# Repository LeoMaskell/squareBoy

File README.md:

# macropad
a macropad! Yet to get the stuff from hackclub as the form is down.

## shell:
- made of abs plastic, constructed with 2 parts, the base and the lid and 4x m3 screws
- onshape document: https://cad.onshape.com/documents/8ea4270e3df64d720bc8c49e/w/e0b07a3a483165cebf54e193/e/cd51b0c8f39a18b2551e130c

## PCB:
- designed in kicad
- 2 layer pcb

## parts list:
- 1x Seeed XIAO RP2040
- 9x through-hole 1N4148 Diodes
- 9x MX-Style switches
- 1x EC11 Rotary encoders
- 1x 0.91 inch OLED display (the pin order is GND-VCC-SCL-SDA, MAKE SURE YOUR PCB MATCHES)
- 9x white blank DSA keycaps
- 4x M3x16mm screws
- 1 PCB
- 2 3d printed parts for the case (dark blue ABS for base plate, light blue ABS for top of shell)

## credits:
- macropad from the website hackpad.hackclub.com -> alex ren, dari.zone
- kicad
- onshape

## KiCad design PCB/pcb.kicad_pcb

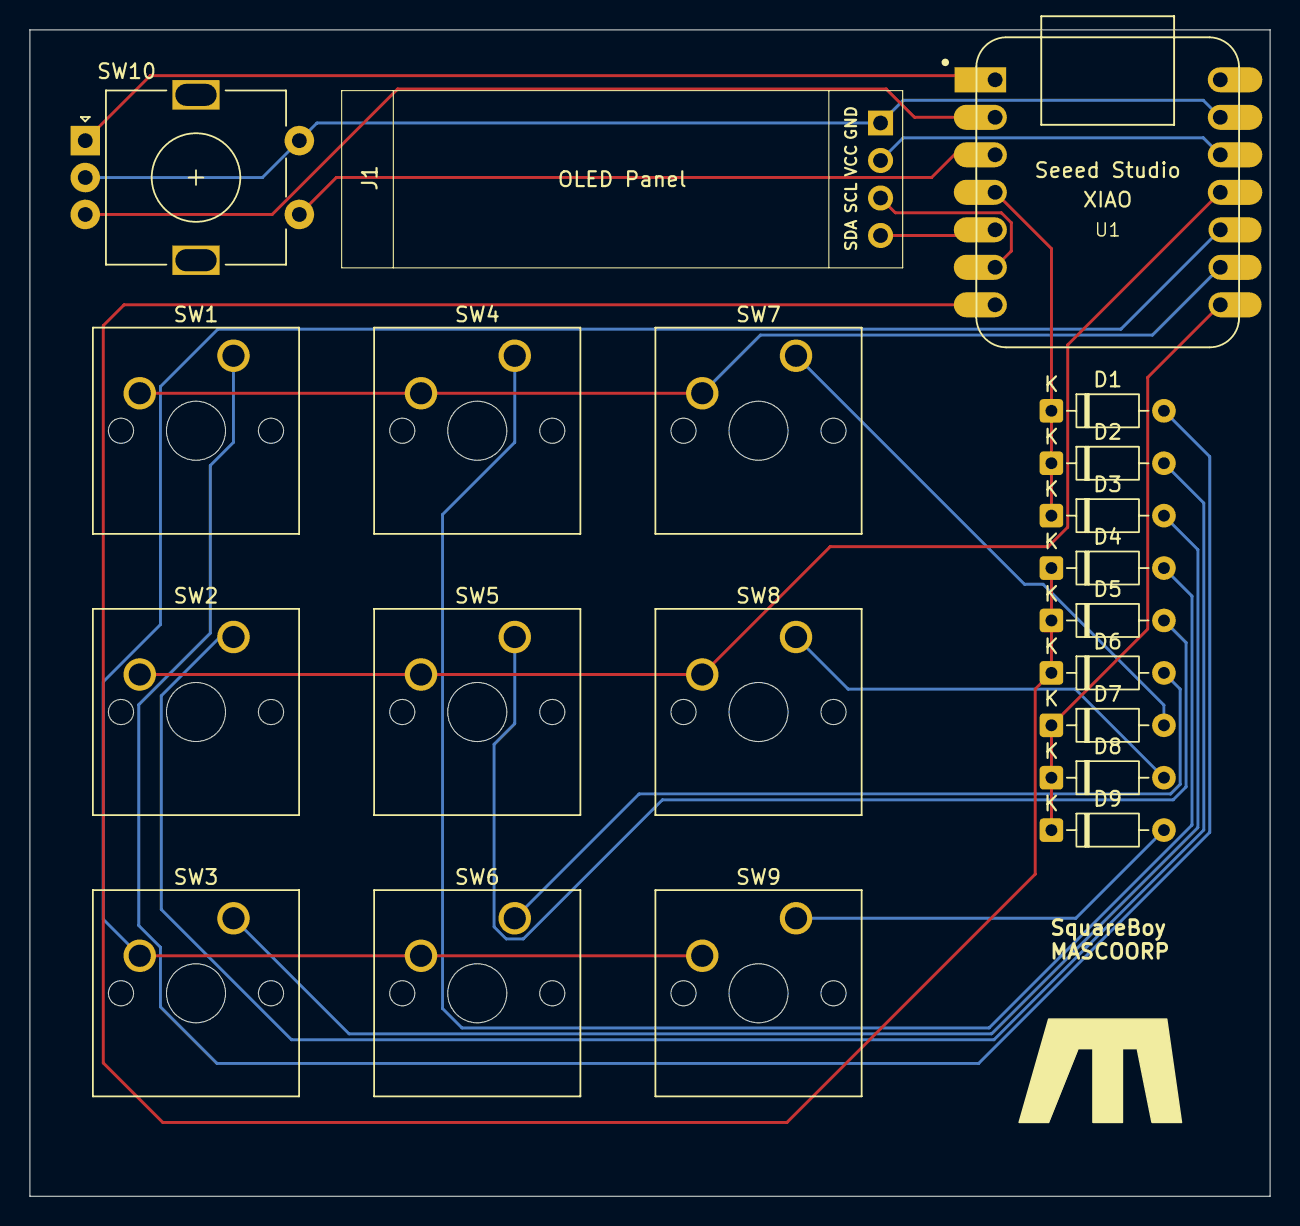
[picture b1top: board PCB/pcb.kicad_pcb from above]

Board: 2 copper layers, 84.0 x 79.0 mm, 21 parts (0 on the bottom side), 22 nets.

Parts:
D1, D2, D3, D4, D5, D6, D7, D8, D9: 1N4148; D_DO-35_SOD27_P7.62mm_Horizontal
J1: Conn_01x04_Pin; SSD1306-0.91-OLED-4pin-128x32(1)
SW1, SW2, SW3, SW4, SW5, SW6, SW7, SW8, SW9: SW_Push; SW_Cherry_MX_1.00u_PCB
SW10: RotaryEncoder_Switch; RotaryEncoder_Alps_EC11E-Switch_Vertical_H20mm
U1: MOUDLE-SEEEDUINO-XIAO; XIAO-Generic-Hybrid-14P-2.54-21X17.8MM

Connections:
unnamed: D1.2 (A), SW1.1
unnamed: D1.1 (K), D2.1 (K), D3.1 (K), U1.4 (PA11_A3_D3)
unnamed: D2.2 (A), SW2.1
unnamed: D3.2 (A), SW3.1
unnamed: D4.2 (A), SW4.1
unnamed: D4.1 (K), D5.1 (K), D6.1 (K), U1.7 (PB08_A6_D6_TX)
unnamed: D5.2 (A), SW5.1
unnamed: D6.2 (A), SW6.1
unnamed: D7.2 (A), SW7.1
unnamed: D7.1 (K), D8.1 (K), D9.1 (K), U1.8 (PB09_A7_D7_RX)
unnamed: D8.2 (A), SW8.1
unnamed: D9.2 (A), SW9.1
unnamed: J1.1, SW10.C, SW10.S2, U1.13 (GND)
unnamed: J1.2, U1.12 (3V3)
unnamed: J1.3, U1.6 (PA9_A5_D5_SCL)
unnamed: J1.4, U1.5 (PA8_A4_D4_SDA)
unnamed: SW10.A, U1.1 (PA02_A0_D0)
unnamed: SW10.B, U1.2 (PA4_A1_D1)
unnamed: SW3.2, SW6.2, SW9.2, U1.10 (PA5_A9_D9_MISO)
unnamed: SW2.2, SW5.2, SW8.2, U1.11 (PA6_A10_D10_MOSI)
unnamed: SW1.2, SW4.2, SW7.2, U1.9 (PA7_A8_D8_SCK)
unnamed: SW10.S1, U1.3 (PA10_A2_D2)

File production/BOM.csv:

"Id";"Designator";"Footprint";"Quantity";"Designation";"Supplier and ref";
1;"D1, D2, D3, D4, D5, D6, D7, D8, D9";"D_DO-35_SOD27_P7.62mm_Horizontal";9;"1N4148";;;
2;"J1";"SSD1306-0.91-OLED-4pin-128x32(1)";1;"Conn_01x04_Pin";;;
3;"SW1, SW2, SW3, SW4, SW5, SW6, SW7, SW8, SW9";"SW_Cherry_MX_1.00u_PCB";9;"SW_Push";;;
4;"SW10";"RotaryEncoder_Alps_EC11E-Switch_Vertical_H20mm";1;"RotaryEncoder_Switch";;;
5;"U1";"XIAO-Generic-Hybrid-14P-2.54-21X17.8MM";1;"MOUDLE-SEEEDUINO-XIAO";;;

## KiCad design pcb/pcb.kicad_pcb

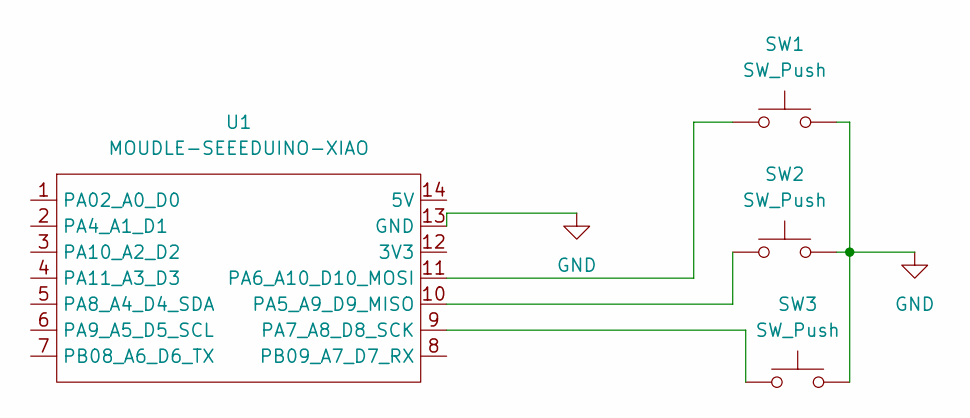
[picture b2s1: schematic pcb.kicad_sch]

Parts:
SW1, SW2, SW3: SW_Push; SW_Cherry_MX_1.00u_PCB
U1: MOUDLE-SEEEDUINO-XIAO; XIAO-Generic-Hybrid-14P-2.54-21X17.8MM

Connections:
GND: SW1.2, SW2.2, SW3.2, U1.13 (GND)
unnamed: SW2.1, U1.10 (PA5_A9_D9_MISO)
unnamed: SW1.1, U1.11 (PA6_A10_D10_MOSI)
unnamed: SW3.1, U1.9 (PA7_A8_D8_SCK)

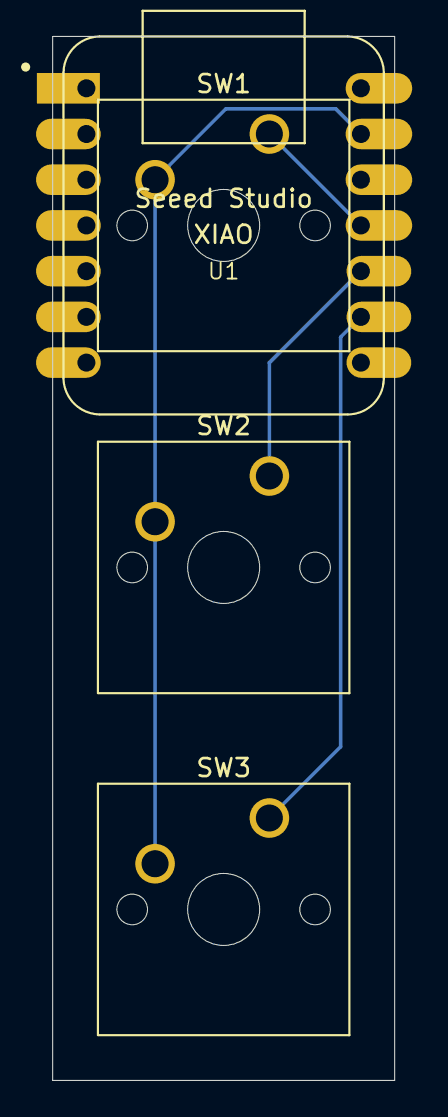
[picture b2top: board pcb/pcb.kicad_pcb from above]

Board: 2 copper layers, 19.0 x 58.0 mm, 4 parts (0 on the bottom side), 4 nets.

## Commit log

2026-06-05 added the pcb
    FIRST PCB!!!!
2026-06-05 finnished pcb, working on the case design for V1
2026-06-06 finnished the template
    TODOL: updae README
2026-06-07 finnished v2
    TODO: V3
    TODO: make pretty and export the onshape files
2026-06-08 Expand README with macropad details
    Added detailed information about the macropad including shell, PCB design, parts list, and credits.
2026-06-08 finnished 3d models etc
2026-06-08 added a release for the demo
2026-06-08 Update README with Onshape document link
    Added Onshape document link for shell design.
2026-06-14 editted PCB
    - added fillets
    - added a silkscreen
    - COMPANY NAME = MASCOORP
    - rewired
    - fixed switch spacing
2026-06-16 added some pcb stuff
    TODO: organise for the thing
2026-06-16 fixed CAD section of the files
2026-06-16 sorted out folders
2026-06-16 finished production except for firmware
2026-06-16 added a BOM for the readme
2026-06-16 Update kit components in README
    Added additional components and images to the kit list.
2026-06-16 Remove duplicate image in README
    Removed duplicate image tag from README.md.
2026-06-16 Add credits section to README
2026-06-17 finished prep
